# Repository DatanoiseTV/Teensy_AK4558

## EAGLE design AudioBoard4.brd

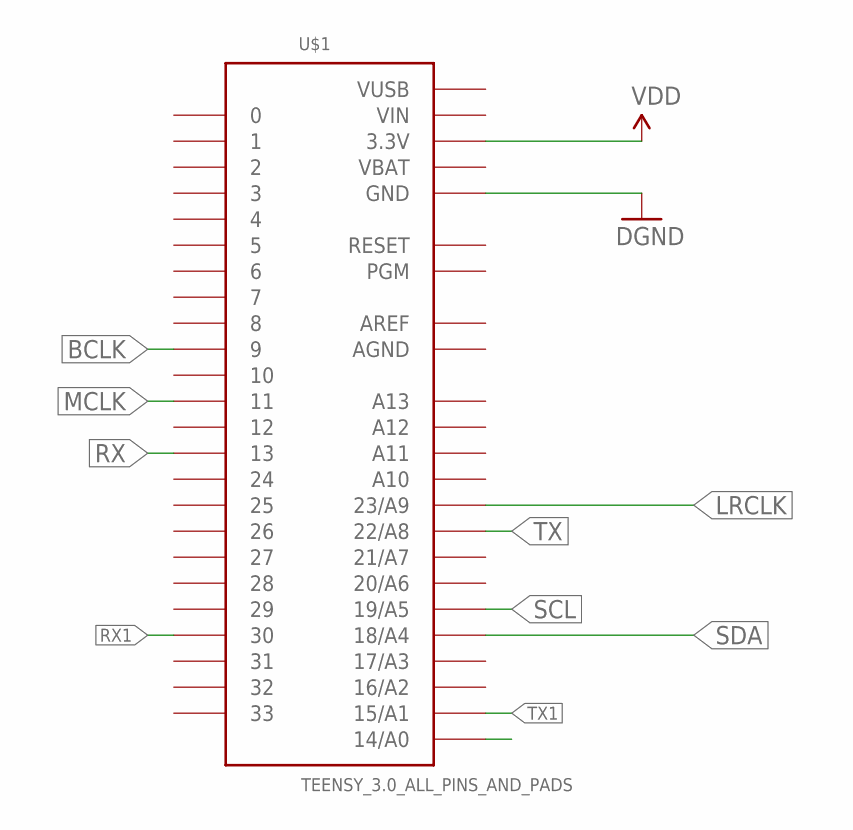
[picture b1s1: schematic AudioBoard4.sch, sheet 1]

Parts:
U$1: TEENSY_3.0_ALL_PINS_AND_PADS; TEENSY_3.0_ALLPINS

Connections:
AGND: U$1.AGND
AREF: U$1.AREF
BCLK: U$1.9; also elsewhere on the board
GND: U$1.GND, U$1.GND1 (GND), U$1.GND2 (GND); also elsewhere on the board
LRCLK: U$1.23/A9; also elsewhere on the board
MCLK: U$1.11; also elsewhere on the board
PDN: U$1.14/A0; also elsewhere on the board
RX: U$1.13; also elsewhere on the board
RX1: U$1.30; also elsewhere on the board
SCL: U$1.19/A5; also elsewhere on the board
SDA: U$1.18/A4; also elsewhere on the board
TX: U$1.22/A8; also elsewhere on the board
TX1: U$1.15/A1; also elsewhere on the board
VBAT: U$1.VBAT
VDD: U$1.3.3V, U$1.3.3V1 (3.3V), U$1.3.3V2 (3.3V); also elsewhere on the board
VIN: U$1.VIN
VUSB: U$1.VUSB

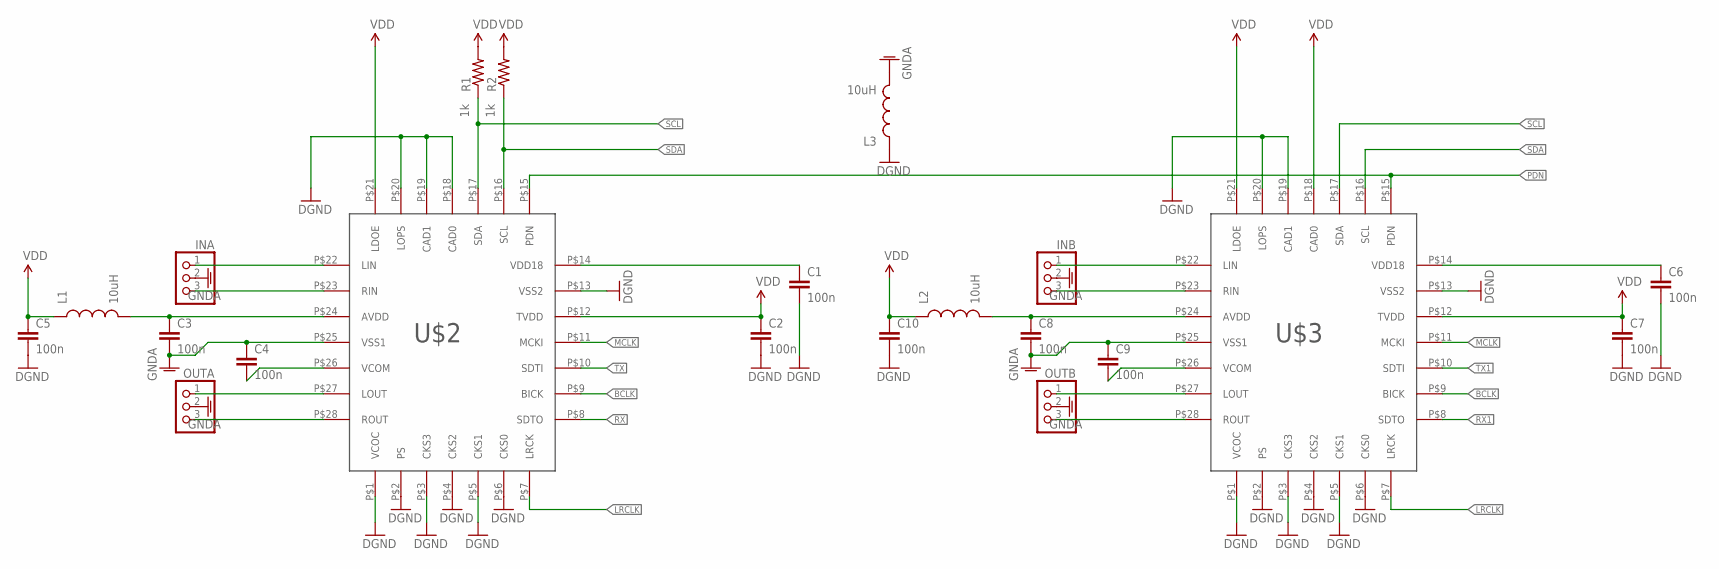
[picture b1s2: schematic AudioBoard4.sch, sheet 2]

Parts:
C1, C2, C3, C4, C5, C6, C7, C8, C9, C10: 100n; 0603-CAP
INA: PINHD-1X3; 1X03
INB: PINHD-1X3; 1X03
L1, L2: 10uH; 0805
L3: 10uH; 0603
OUTA: PINHD-1X3; 1X03
OUTB: PINHD-1X3; 1X03
R1, R2: 1k; 0603-RES
U$2, U$3: AK4558EN; QFN-28-5MM

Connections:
BCLK: U$2.P$9 (BICK), U$3.P$9 (BICK); also elsewhere on the board
GND: C1.2, C2.2, C5.2, C6.2, C7.2, C10.2, L3.1, U$2.P$1 (VCOC), U$2.P$2 (PS), U$2.P$3 (CKS3), U$2.P$4 (CKS2), U$2.P$5 (CKS1), U$2.P$6 (CKS0), U$2.P$13 (VSS2), U$2.P$18 (CAD0), U$2.P$19 (CAD1), U$2.P$20 (LOPS), U$3.P$1 (VCOC), U$3.P$2 (PS), U$3.P$3 (CKS3), U$3.P$4 (CKS2), U$3.P$5 (CKS1), U$3.P$6 (CKS0), U$3.P$13 (VSS2), U$3.P$19 (CAD1), U$3.P$20 (LOPS); also elsewhere on the board
GNDA: C3.2, C4.1, C8.2, C9.1, INA.2, INB.2, L3.2, OUTA.2, OUTB.2, U$2.P$25 (VSS1), U$3.P$25 (VSS1)
LRCLK: U$2.P$7 (LRCK), U$3.P$7 (LRCK); also elsewhere on the board
MCLK: U$2.P$11 (MCKI), U$3.P$11 (MCKI); also elsewhere on the board
unnamed: C1.1, U$2.P$14 (VDD18)
unnamed: C3.1, L1.2, U$2.P$24 (AVDD)
unnamed: C4.2, U$2.P$26 (VCOM)
unnamed: INA.1, U$2.P$22 (LIN)
unnamed: INA.3, U$2.P$23 (RIN)
unnamed: OUTA.1, U$2.P$27 (LOUT)
unnamed: OUTA.3, U$2.P$28 (ROUT)
unnamed: C6.1, U$3.P$14 (VDD18)
unnamed: C8.1, L2.2, U$3.P$24 (AVDD)
unnamed: C9.2, U$3.P$26 (VCOM)
unnamed: INB.1, U$3.P$22 (LIN)
unnamed: INB.3, U$3.P$23 (RIN)
unnamed: OUTB.1, U$3.P$27 (LOUT)
unnamed: OUTB.3, U$3.P$28 (ROUT)
PDN: U$2.P$15 (PDN), U$3.P$15 (PDN); also elsewhere on the board
RX: U$2.P$8 (SDTO); also elsewhere on the board
RX1: U$3.P$8 (SDTO); also elsewhere on the board
SCL: R1.1, U$2.P$17 (SDA), U$3.P$17 (SDA); also elsewhere on the board
SDA: R2.1, U$2.P$16 (SCL), U$3.P$16 (SCL); also elsewhere on the board
TX: U$2.P$10 (SDTI); also elsewhere on the board
TX1: U$3.P$10 (SDTI); also elsewhere on the board
VDD: C2.1, C5.1, C7.1, C10.1, L1.1, L2.1, R1.2, R2.2, U$2.P$12 (TVDD), U$2.P$21 (LDOE), U$3.P$12 (TVDD), U$3.P$18 (CAD0), U$3.P$21 (LDOE); also elsewhere on the board

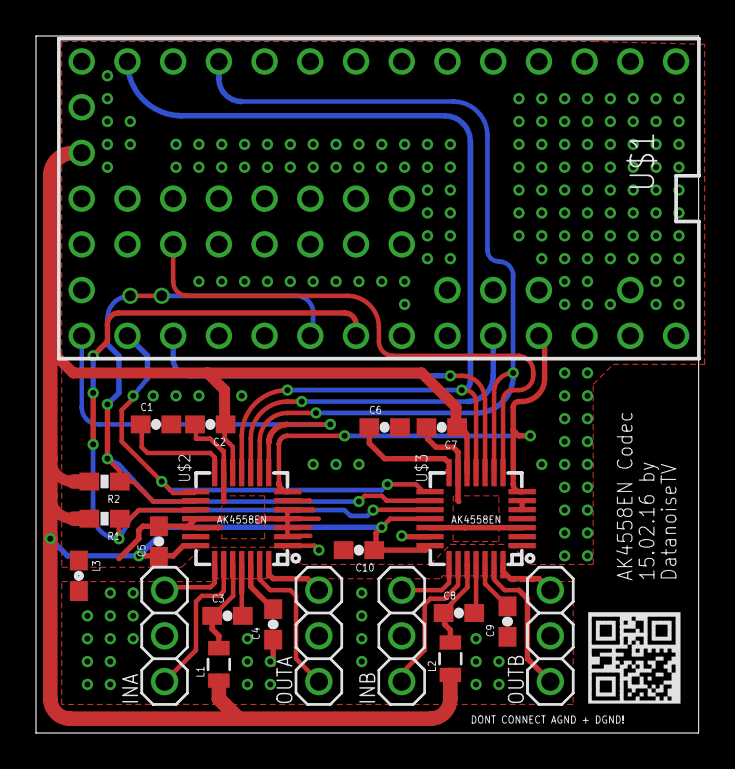
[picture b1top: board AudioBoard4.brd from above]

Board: 2 copper layers, 36.8 x 38.7 mm, 22 parts (0 on the bottom side), 27 nets.

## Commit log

2016-02-15 Add initial files.
2016-02-18 Update eagle files to contain powerdown signal.

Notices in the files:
parts and their libraries:
SparkFun-Passives: Licensing: Creative Commons ShareAlike 4.0 International - https://creativecommons.org/licenses/by-sa/4.0
